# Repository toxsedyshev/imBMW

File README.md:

imBMW · BMW iBus integration SDK and hardware
=========================

[imBMW]: http://imBMW.net "imBMW"
[toxs]: http://toxs.ru "toxs"

[imBMW] is .NET Micro Framework and hardware project. It was started to add custom features to cars with **iBus** interface such as '91-'10 BMWs and some models of Mini, Land Rover, Rover, MG and Rolls Royce. Then **CAN BUS** support was added to integrate with newer F,I,G-series BMWs.

The Original **imBMW V1** device uses **FEZ Mini**, connects with iPod/iPhone via headset cable to be controlled by BMW audio system.

The Next Gen **imBMW V2** device, that uses **STM32F405** based **FEZ Cerb40 II**, is a *duino-compatible iBus-ready board. It could be used with any shield, for example with **imBMW Bluetooth OVC3860** or **Bluetooth Pro Bluegiga WT32 Shields** for wireless stereo audio connection to BMW audio system, handsfree calls and even for forwarding iBus via Bluetooth to smartphones, tablets and PCs - imBMW already has a library for **Universal Windows Platform (UWP)**. There is also **Diagnostic Bus DS2** support using regular OBD II to USB adapter, that allows Engine Control Unit plus additional sensors logging and wireless Bluetooth dashboard. Furthermore, **CAN BUS** support was added for sniffing and integrating with CAN modules of all BMWs since the end 90's till latest BMW models including i-series EVs — for example, CAN BUS integration allowed to [integrate BMW E65 full comfort seats into older BMW E53](https://www.youtube.com/watch?v=P0yJuep_bd4&list=PLDuwqawzvazj9iFQQ9aeggeXeUPphfv94&index=5&pp=gAQBiAQB).

CD-changer emulator and Bordmonitor AUX interface were implemented to connect radio with iPod/iPhone/iPad or with other players, phones and tablets like Windows Phone, Android etc. 
Also imBMW allows communicating with instrument cluster, immobilizer, GM, ZKE, navigation and other modules to receive notifications and control doors, windows, lights, etc.

How to buy imBMW
------------------
**Please note: I used to manufacture and sell imBMW devices but I DON'T sell them anymore.**

You can DIY the project for your personal use as many community members did, some [examples of the device forks are shown here](https://vk.com/album-67915700_260588402).

Social networks
-----------------
* Visit [imBMW YouTube playlist](http://www.youtube.com/playlist?list=PLDuwqawzvazj9iFQQ9aeggeXeUPphfv94) on my channel.
* Official group: [imBMW on vk.com](http://vk.com/imbmw).
* Stay in touch via [imbmw@toxs.ru](mailto:imbmw@toxs.ru), but please remember: I don't sell devices anymore. 
* Photos, videos and creation process of imBMW V1 and V2 devices are located on [e46club.ru forum](http://bmwfanatics.ru/forumvb/viewtopic.php?f=32&t=92399) (for now, only in Russian).

Photos
-

Some screens for example. Playing Bluetooth music, custom bordcomputer, additional features, english and russian UI:  

imBMW compatability
------------------

iBus-compatible cars are listed below:
* BMW 3-series E46, E36*
* BMW 5-series E39, E34*, E60*
* BMW 7-series E38
* BMW 8-series E31*
* BMW X3 E83
* BMW X5 E53
* BMW Z4 E85, E86
* BMW Z8 E52
* MINI Cooper R50, Cooper S R53
* Land Rover Range Rover L30
* Rover 75 R40
* Saab 9-3 2003+

Notes:
* E31 uses different device IDs.
* Last 2 production years of E36 and E34 had iBus-controlled CD43 radio and CD-changers.
* E60 ver. USA had iBus-controlled seat occupation sensor.

imBMW license
------------------

[imBMW] is developed by [toxs] and distributed under Open Source
[CC Attribution Non-Commercial Share Alike License](http://creativecommons.org/licenses/by-nc-sa/3.0/). 
This basically means:
* Licensees may copy, distribute, display and perform the work and make derivative works 
based on it only if they give the author or licensor the credits in the manner specified by these.
* Licensees may copy, distribute, display, and perform the work and make derivative works 
based on it only for noncommercial purposes.
* Licensees may distribute derivative works only under a license identical to the license 
that governs the original work.

© Copyright 2013-2014 [toxs] · All Rights Reserved

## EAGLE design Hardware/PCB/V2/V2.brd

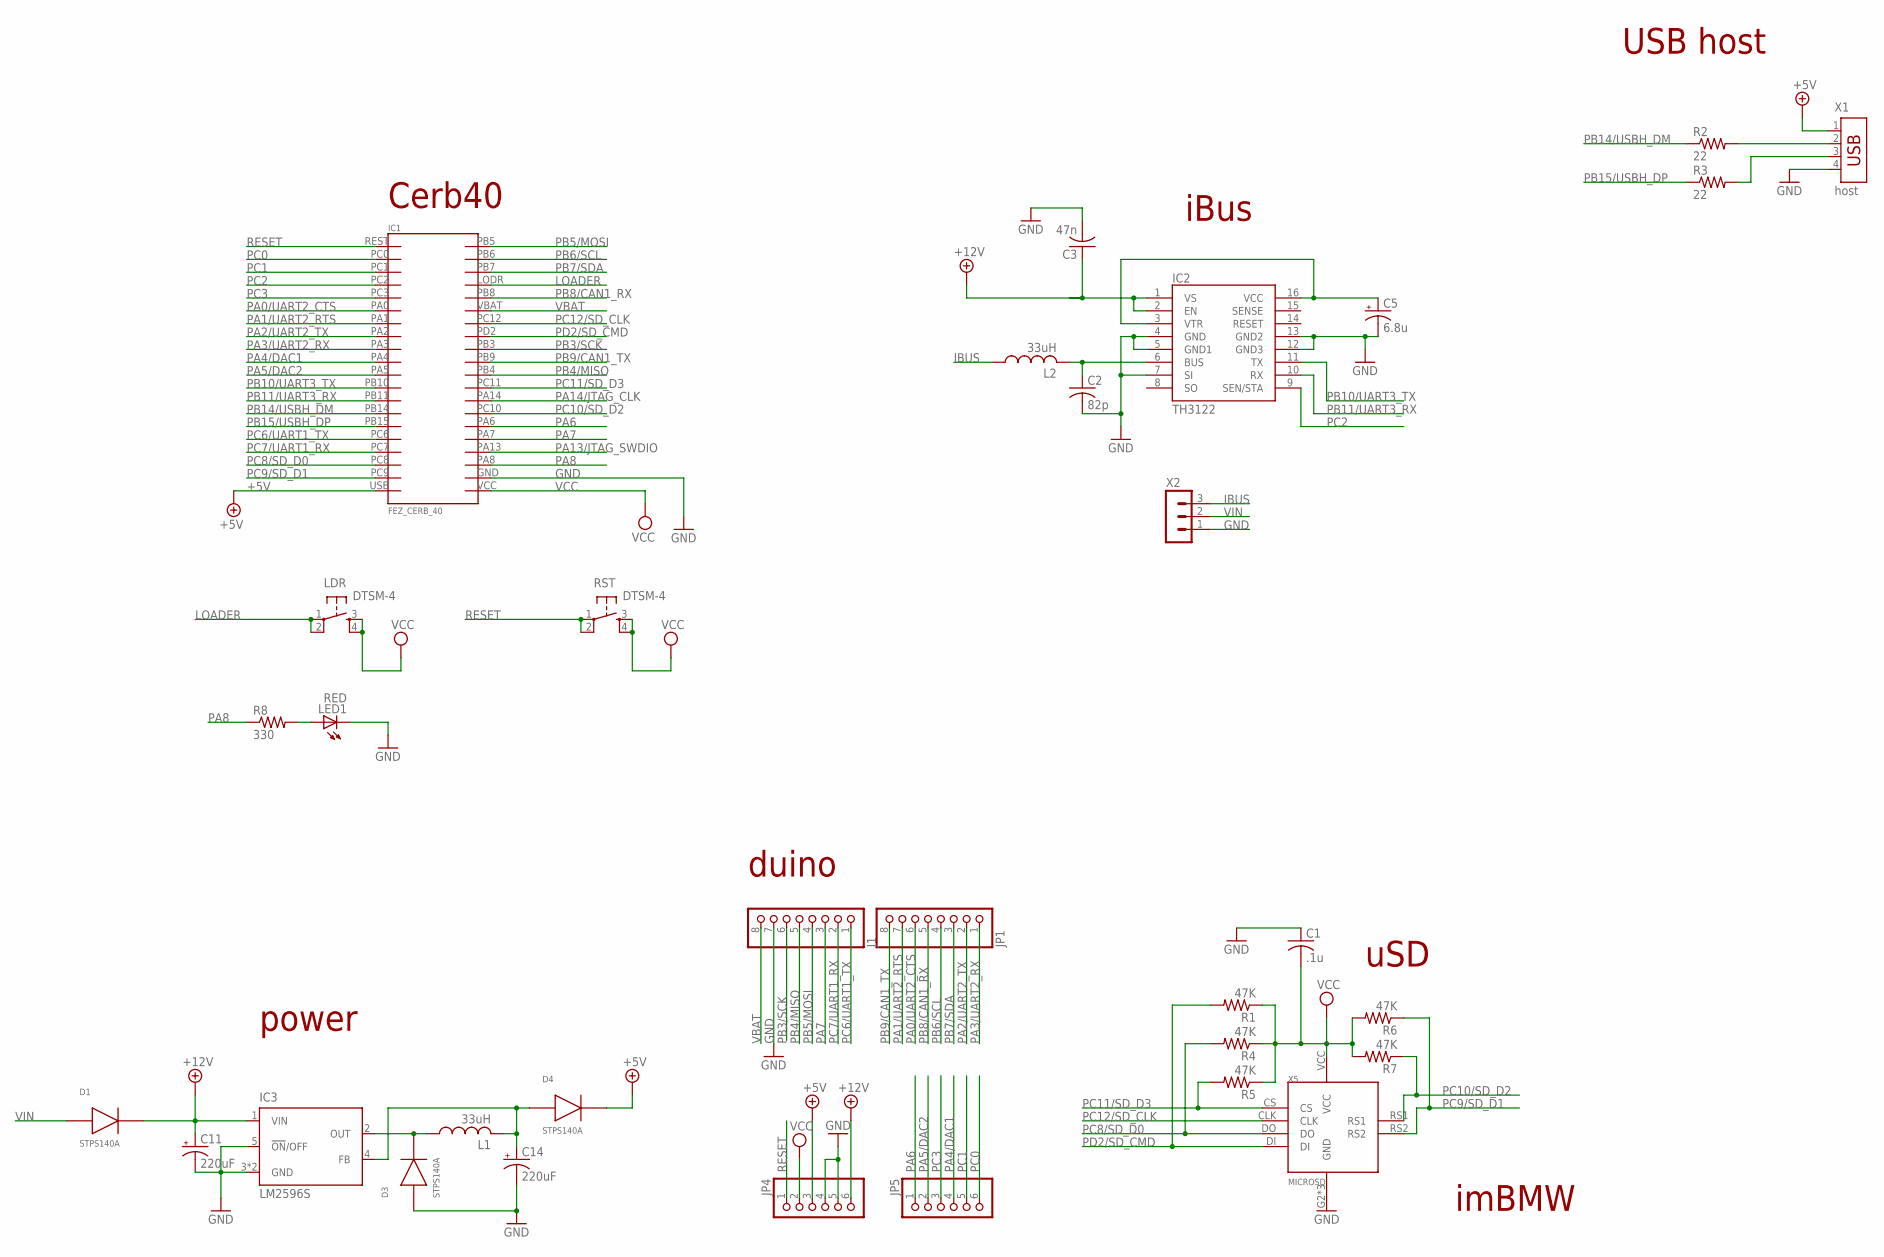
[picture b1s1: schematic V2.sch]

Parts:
C1: .1u; C0805
C2: 82p; C0805
C3: 47n; C0805
C5: 6.8u; SMC_B
C11, C14: 220uF; SMC_D
D1, D3, D4: STPS140A; DIODE_SMA
IC1: FEZ_CERB_40
IC2: TH3122; SO16L
IC3: LM2596S; TO263-5
J1: PINHD-1X8; 1X08
JP1: PINHD-1X8; 1X08
JP4, JP5: PINHD-1X6; 1X06
L1, L2: 33uH; POWER-CHOKE_WE-TPC
LDR: DTSM-4
LED1: RED; SML0603
R1, R4, R5, R6, R7: 47K; R0805
R2, R3: 22; R0805
R8: 330; R0805
RST: DTSM-4
X1: host; USB
X2: MA03-1
X5: MICROSD

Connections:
+5V: D4.K, IC1.USB, JP4.3, X1.1
+12V: C3.1, C11.+, D1.K, IC2.1 (VS), IC2.2 (EN), IC3.1 (VIN), JP4.6
GND: C1.1, C2.2, C3.2, C5.-, C11.-, C14.-, D3.A, IC1.GND, IC2.4 (GND), IC2.5 (GND1), IC2.7 (SI), IC2.12 (GND3), IC2.13 (GND2), IC3.3 (GND), IC3.5 (!ON!/OFF), IC3.6 (GND), J1.7, JP4.4, JP4.5, LED1.C, X1.4, X2.1, X5.G2 (GND), X5.G3 (GND), X5.GND
IBUS: L2.1, X2.3
LOADER: IC1.LODR, LDR.1, LDR.2
unnamed: C14.+, D4.A, IC3.4 (FB), L1.2
unnamed: C2.1, IC2.6 (BUS), L2.2
unnamed: D3.K, IC3.2 (OUT), L1.1
unnamed: C5.+, IC2.3 (VTR), IC2.16 (VCC)
unnamed: LED1.A, R8.2
unnamed: R2.2, X1.2
unnamed: R3.2, X1.3
PA0/UART2_CTS: IC1.PA0, JP1.6
PA1/UART2_RTS: IC1.PA1, JP1.7
PA2/UART2_TX: IC1.PA2, JP1.2
PA3/UART2_RX: IC1.PA3, JP1.1
PA4/DAC1: IC1.PA4, JP5.4
PA5/DAC2: IC1.PA5, JP5.2
PA6: IC1.PA6, JP5.1
PA7: IC1.PA7, J1.3
PA8: IC1.PA8, R8.1
PA13/JTAG_SWDIO: IC1.PA13
PA14/JTAG_CLK: IC1.PA14
PB3/SCK: IC1.PB3, J1.6
PB4/MISO: IC1.PB4, J1.5
PB5/MOSI: IC1.PB5, J1.4
PB6/SCL: IC1.PB6, JP1.4
PB7/SDA: IC1.PB7, JP1.3
PB8/CAN1_RX: IC1.PB8, JP1.5
PB9/CAN1_TX: IC1.PB9, JP1.8
PB10/UART3_TX: IC1.PB10, IC2.11 (TX)
PB11/UART3_RX: IC1.PB11, IC2.10 (RX)
PB14/USBH_DM: IC1.PB14, R2.1
PB15/USBH_DP: IC1.PB15, R3.1
PC0: IC1.PC0, JP5.6
PC1: IC1.PC1, JP5.5
PC2: IC1.PC2, IC2.9 (SEN/STA)
PC3: IC1.PC3, JP5.3
PC6/UART1_TX: IC1.PC6, J1.1
PC7/UART1_RX: IC1.PC7, J1.2
PC8/SD_D0: IC1.PC8, R4.2, X5.DO
PC9/SD_D1: IC1.PC9, R6.1, X5.RS2
PC10/SD_D2: IC1.PC10, R7.1, X5.RS1
PC11/SD_D3: IC1.PC11, R5.2, X5.CS
PC12/SD_CLK: IC1.PC12, X5.CLK
PD2/SD_CMD: IC1.PD2, R1.2, X5.DI
RESET: IC1.REST, JP4.1, RST.1, RST.2
VBAT: IC1.VBAT, J1.8
VCC: C1.2, IC1.VCC, JP4.2, LDR.3, LDR.4, R1.1, R4.1, R5.1, R6.2, R7.2, RST.3, RST.4, X5.VCC
VIN: D1.A, X2.2

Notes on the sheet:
imBMW
uSD
duino
power
USB host
iBus
Cerb40

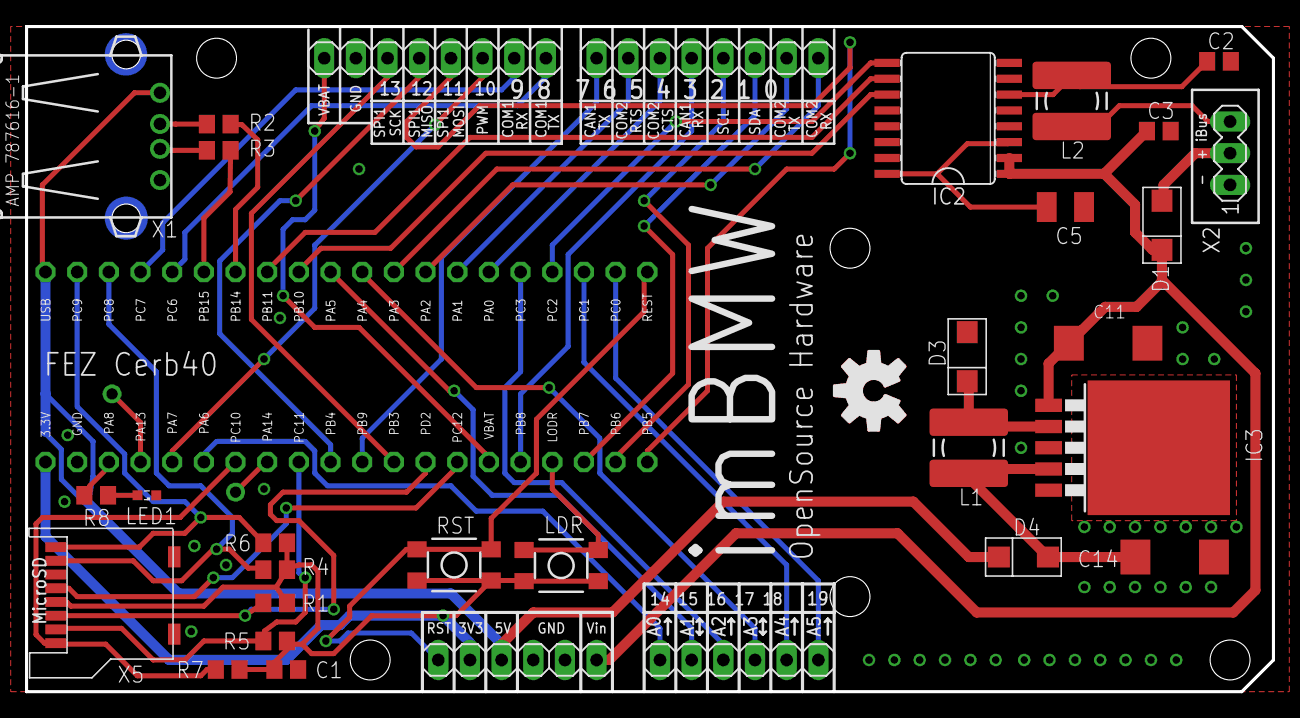
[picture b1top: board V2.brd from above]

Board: 2 copper layers, 100.0 x 53.3 mm, 32 parts (0 on the bottom side), 48 nets.

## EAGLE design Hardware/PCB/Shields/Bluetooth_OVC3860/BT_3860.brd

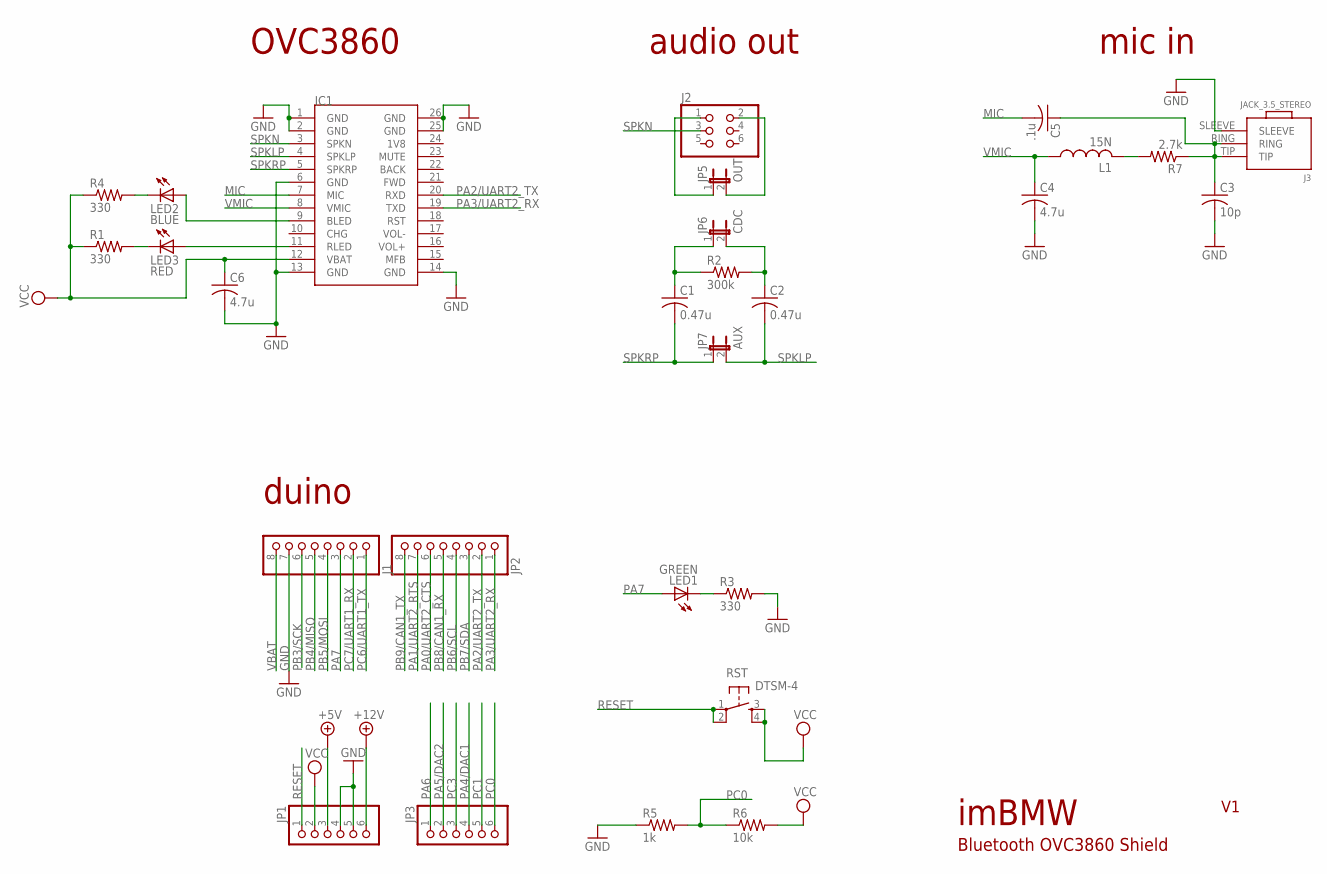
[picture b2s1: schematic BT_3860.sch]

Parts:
C1, C2: 0.47u; C0805
C3: 10p; C0805
C4, C6: 4.7u; C0805
C5: .1u; C0805
IC1: BLK-MD-SPK-B
J1: PINHD-1X8; 1X08
J2: PINHD-2X3; 2X03
J3: JACK_3.5_STEREO
JP1, JP3: PINHD-1X6; 1X06
JP2: PINHD-1X8; 1X08
JP5: OUT; JP1
JP6: CDC; JP1
JP7: AUX; JP1
L1: 15N; L3230M
LED1: GREEN; SML0603
LED2: BLUE; SML0603
LED3: RED; SML0603
R1, R3, R4: 330; R0805
R2: 300k; R0805
R5: 1k; R0805
R6: 10k; R0805
R7: 2.7k; R0805
RST: DTSM-4

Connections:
+5V: JP1.3
+12V: JP1.6
GND: C3.2, C4.2, C6.2, IC1.1 (GND), IC1.2 (GND), IC1.6 (GND), IC1.13 (GND), IC1.14 (GND), IC1.25 (GND), IC1.26 (GND), J1.7, J3.SLEEVE, JP1.4, JP1.5, R3.2, R5.1
MIC: C5.2, IC1.7 (MIC)
unnamed: C2.1, JP6.2, R2.2
unnamed: C1.1, JP6.1, R2.1
unnamed: J2.1, JP5.1
unnamed: J2.2, JP5.2
unnamed: LED1.C, R3.1
unnamed: LED3.C, R1.2
unnamed: IC1.11 (RLED), LED3.A
unnamed: IC1.9 (BLED), LED2.A
unnamed: LED2.C, R4.2
unnamed: C3.1, C5.1, J3.RING, J3.TIP, R7.1
unnamed: L1.2, R7.2
PA0/UART2_CTS: JP2.6
PA1/UART2_RTS: JP2.7
PA2/UART2_TX: IC1.20 (RXD), JP2.2
PA3/UART2_RX: IC1.19 (TXD), JP2.1
PA4/DAC1: JP3.4
PA5/DAC2: JP3.2
PA6: JP3.1
PA7: J1.3, LED1.A
PB3/SCK: J1.6
PB4/MISO: J1.5
PB5/MOSI: J1.4
PB6/SCL: JP2.4
PB7/SDA: JP2.3
PB8/CAN1_RX: JP2.5
PB9/CAN1_TX: JP2.8
PC0: JP3.6, R5.2, R6.1
PC1: JP3.5
PC3: JP3.3
PC6/UART1_TX: J1.1
PC7/UART1_RX: J1.2
RESET: JP1.1, RST.1, RST.2
SPKLP: C2.2, IC1.4 (SPKLP), JP7.2
SPKN: IC1.3 (SPKN), J2.3
SPKRP: C1.2, IC1.5 (SPKRP), JP7.1
VBAT: J1.8
VCC: C6.1, IC1.12 (VBAT), JP1.2, R1.1, R4.1, R6.2, RST.3, RST.4
VMIC: C4.1, IC1.8 (VMIC), L1.1

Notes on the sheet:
imBMW
duino
Bluetooth OVC3860 Shield
OVC3860
audio out
mic in

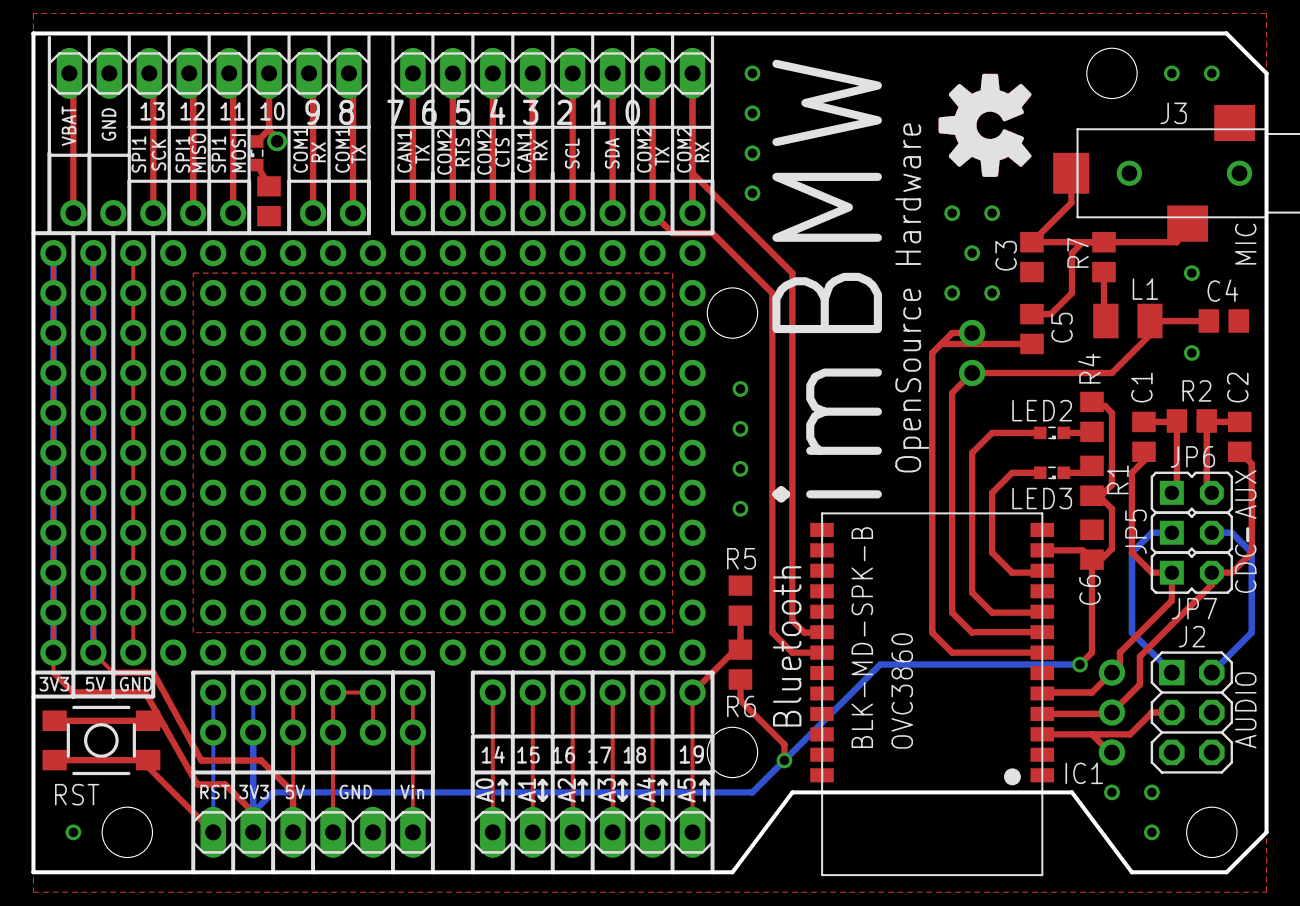
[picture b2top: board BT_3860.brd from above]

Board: 2 copper layers, 78.4 x 53.3 mm, 28 parts (0 on the bottom side), 23 nets.

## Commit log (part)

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2013-01-05 Readme added
2013-01-07 Added iPod control
2013-01-10 Connected MFL to iPod, added iBus messages descriptions
2013-01-11 Fixed RT press, cleaned up Program.cs
2013-01-11 Fixed Dial long press
2013-01-11 Removed unnecessary sleep
2013-01-12 Added CDC play/pause, fixed Dial long press, added status displaying
2013-01-15 IKE logic moved to its own class
2013-01-16 MFL logic moved to its own class
2013-01-18 Schematics and PCB design added
2013-01-24 ManualResetEvent added to QueueThreadWorker
2013-01-26 PCB updated
2013-01-28 Added display text for playing state fix by RND button
2013-01-29 QueueWorkerThread priority fix
    Trying to fix *ResetEvent slowness
2013-01-29 ClassDiagram added and PCB updated
2013-02-03 Cleaned up the code
2013-02-04 Logger added
2013-02-05 License changed
2013-02-05 GC logs turned off
2013-02-17 Clear radio display on turning off
2013-02-17 iPod logic moved to its own class
2013-02-25 Trunk opening added.
2013-02-28 Readme changed
2013-03-01 imBMW library and imBMW V1 device separated to different projects
2013-03-01 IKE: Speed&RPM. Doors: lock/unlock.
2013-03-01 Feature: Close doors on 5km/h, open on ignition off
2013-03-01 Feature: close windows and sunroof when car is locked from remote.
2013-03-04 Fixed ignition, created Comfort Features class
    ...for auto open/close doors, windows, sunroof, mirrors
2013-03-07 Added message received/sent events, description
2013-03-09 iBus manager fixes
    Write enqueue recursion, read queue, anti-flood 20ms
2013-03-10 Readme fix
2013-03-15 Write anti-flood changed to 5ms, read processing moved to the main thread
2013-03-19 SerialPorts fixes
2013-03-22 Batch iBus sending, PerformanceInfo, SampleFeatures
2013-03-22 SerialInterruptPort glitch fix, QueueThreadWorker normal priority
2013-03-28 SerialPorts fixes and optimization. Some cleanup
2013-03-30 iBus batch read, SerialPorts fixes, SerialPortHub works
2013-03-30 SerialPortHub fix
2013-03-31 Logs deleted
2013-03-31 Comfort features commands queue. Blink LED on I/O.
2013-04-03 SerialPortBase.WriteTimeout renamed to AfterWriteDelay
2013-04-12 ReadMe updated
2013-04-26 iBus optopair adapter pcb added
2013-04-29 iBus optopair adapter pcb updated
2013-05-07 XPS for toner transfer method of V1 PCB added
2013-05-12 Added LightControlModule and some fixes
2013-07-21 iBus AfterWriteDelay fix, CDC play/pause fix, comfort close fix
2013-11-29 Initial commit of V2
2013-11-29 SerialPorts (OptoPair). Some other fixes.
    SerialInterruptPortBase, SerialPortOptoPair, SerialTimerInterruptPort
2013-12-27 Added support of BT OVC3860
    Bluetooth module Bolutek BLK-MD-SPK-B based on OmniVision OVC3860
2014-01-07 Bluetooth fixes
2014-02-01 Added Bordmonitor support (partial), Russian text
    and other fixes
2014-02-20 Little fix: namespace changed
2014-02-22 Extending platform
    Added SeatMemory, Navigation IBus device message parsing.
2014-02-22 AUX detection, players' events displaying
2014-03-18 Find device on iBus, Bluetooth fixes, Contacts parsing, Temperature, Voltage
    Unstable
2014-03-20 Custom BC fixes
2014-03-21 Readme fixed
2014-03-21 Readme changed. Again
2014-04-03 Added screenshot to readme.
2014-04-21 Bordmonitor menu. MID screen. Sheilds (draft).
2014-04-27 BM menu fixes.
2014-05-04 Rad menu flickering fix. Bordcomputer and settings screens. BT connect fix and contacts screen. Localization. CDC fix. Door and key commands. Temp fix.
2014-05-05 Remote key buttons fix
2014-05-05 CDC+AUX=MediaEmulator.
    Not tested!
2014-05-06 MB menu flickering fixes. CDC emulation fixes. Init fixed.
    + Driver door lock. Gong messages. Menu checkbox fixes.
    Not tested!
2014-05-06 CDC emulation fixes. BT connect&play fix.
2014-05-06 Added version info.
2014-05-06 [SW V1.0] Added hex binaries
2014-05-06 Some strings
2014-05-19 Code cleanup, added additional modules
2014-05-19 Revert back changes to original distribution
2014-05-22 MenuScreenUpdateReason, Settings, etc..
    ..lock/unlock doors fixes, contacts reading refactored, FileLogger
    (unstable)
2014-05-23 RadioMenu added, Contacts fixed, MK2 fixed, V1 device updated
2014-05-23 RadioMenu BC fix
2014-05-27 RadioMenu fixes, .NET MF 4.1 fixes
2014-05-28 BC voltage auto update
2014-05-28 Added HW2 FW1.0.3 build
2014-06-05 Radio menu: track change fixed, BC screen fixed.
2014-06-08 Radio menu track change fixed
2014-06-08 Added HW2 FW1.0.5 build
2014-06-15 Readme images changed
2014-06-30 BordmonitorMenu and RadioMenu fixed
2014-07-16 Added HW2 FW1.0.7 build
2014-07-19 Radio MFL navigation fixed. Device V2 pins added. Tests added.
2014-07-19 Bordmonitor batch writing.
2014-07-19 BC voltage fix.
2014-07-19 GM5 unlock fix
2014-07-19 Added HW2 FW1.0.8 build
2014-09-03 Bordmonitor batch screen update in single message
2014-09-03 Added HW2 FW1.0.9 build
2014-10-19 Project structure changed
2014-10-19 Added V2 and Bluetooth OVC3860 Eagle projects. Added case projects. Builds moved.
2014-10-31 Bluetooth WT32 initial work.
2014-11-04 WT32 implemented as AudioPlayer.
2014-11-06 NowPlaying WT32 parsing.
2014-11-06 Translit and Yo ASCII support added for Russian. NowPlaying on Bordmonitor fixed.
2014-11-07 WT32 fixes. Menu fixes.
2014-11-09 Fixed iBus message max length.
2014-11-09 WT32 MUX mode.
2014-11-11 UTF8 to ASCII optimized.
2014-11-11 Added support for player settings status event.
2014-11-12 SerialInterruptPort fixed.
2014-11-12 iBus.Manager can send raw messages.
2014-11-12 WT32 SPPLink added.
2014-11-14 .NET MF library preparations for Portable .NET library. InternalMessage.
2014-11-14 .NET Portable library initial commit.
2014-11-14 WindowsPhone/Windows Universal App initial commit.
2014-11-14 iBus.Manager static constructor fixes.
2014-11-14 SPPLink fix.
2014-11-14 BluetoothClient added to imBMW.Portable.
2014-11-21 Bordmonitor show text events.
2014-11-21 PCL BT Client fixes.
2014-11-21 WindowsApp BT connection. Bordmonitor and Test pages.
2014-11-23 Comfort windows fixed to prevent ignoring by ZKE.
2014-11-23 BM<>Radio buttons and events.
2014-11-23 SharedApp Bordmonitor and Test Pages fixed.
2014-11-24 SharedApp logger fixed.
2014-11-24 BM&Radio commands fixed.
2014-11-24 WT32 pin change support.
2014-11-24 SocketClient fixed.
2014-11-24 SharedApp: assets updated.
2014-11-24 BluetoothPin added to settings.
2014-11-24 MediaShield setting added.
2014-11-24 InternalCommunications.
2014-11-24 MessageParser used in SocketClient.
2014-11-26 Readme changed.
2015-01-22 Build 1.0 files renamed
2015-01-22 Full windows open command fixed
2015-01-22 PCL logger implemented
2015-01-22 Added Init() for static iBus device classes
2015-01-22 Bordmonitor fixed item indexes and parsing
2015-01-22 SharedApp: LoggerPage added
2015-02-01 V2 device pins refactored.
2015-02-01 Manager.FindDevice refactored with ManualResetEvent
2015-04-03 Unlock doors after driver door opened reverted.
2015-04-10 Device.V1 .NET MF 4.1 memory limit fixes
2015-06-11 OVC3860 autoplay fixed.
2015-06-11 WT32 HFP enabled.
2015-06-11 Some non-functional fixes.
2015-06-11 Version string fixed.
2015-06-11 Added HW2 FW1.0.10 build
2015-07-09 MK2 and MK3 menu drawing fixed.
2015-07-10 Added HW2 FW1.0.11 build
2015-09-17 Updated to GHI SDK 2015 R1 (4.3.7.10)
2015-10-12 DBus DS2 initial commit
2015-10-13 NETMF 4.1 fixed V1.Program and StringHelpers
2015-10-14 DBus moved to separate project. MS43 analog values parsing started.
2015-10-14 MS43 analog values parsed
2015-10-19 MS43 logger strings and fixes
2015-10-23 Added JMGarage patched DME diag parser
2015-11-24 Fixed iBus.Message checksum
2015-11-24 Date&Time and BC parsing
    Partly merged huge pull request by @arctus
2016-04-05 DateTime parsing fixed for US locale.
2016-04-05 MID menu buttons added.
2016-04-05 QueueThreadWorker made public.
2016-04-10 DateTime parse 12PM fixed.
2016-04-14 Added mask to MID menu last buttons.
2016-04-14 Fixed battery voltage on BC.
2016-04-14 BC: unset values fixed and unchanged events not fired.
2016-04-15 BC: added original BC values to BC screen.
2016-04-20 Main imBMW project splitted to multiple projects.
    To reduce dlls size - .NET MF limit.
2016-04-21 Bordmonitor translit fix.
2016-04-21 BC limit fix.
2016-04-21 Readme changed with new BC screens.
2016-04-21 BC: unset values fixed.
2016-04-21 Added HW2 FW1.0.12 build
2016-06-12 Diagnostic fixes and cleanup.
2016-06-12 Some cleanup.
2016-06-12 Starting to port PCL to UWP.
2016-07-27 Starting the Dashboard.
2016-08-04 Gauges updated.
2016-08-05 Gauge updated.
2016-08-05 PieSlice double gauge support.
2016-08-08 DoubleGauge implemented.
2016-08-10 Default settings for gauges.
2016-08-10 Dashboard fixes.
2016-08-12 TestGauges fixed.
2016-08-14 Dashboard link from Home.
2016-08-14 DBus message fixes.
2016-08-14 Messages fixed.
2016-08-14 GaugeWatcher fixed.
2016-08-15 Dashboard fixed.
2016-08-15 DBusMessageParser fixed.
2016-08-15 UWP Hashtable fix.
2016-08-15 Mobile Dashboard added.
2016-08-15 Some fixes for UWP App.
2016-08-16 SecondaryGauge update by GaugeField fix.
2016-11-29 RadioMenu RT mode fix.
2016-11-29 UWP app updated.
2017-03-30 MFL player control fixed with CDC and Bordmonitor.
2017-03-30 Cerberus parity bug fixed in the firmware. Finally.
2018-01-22 BC fix for non-E46 IKEs
    By @windel12
2018-03-07 Gauges refactored (partly)
2018-03-07 Partial revert of a21c8ff commit
2018-04-16 References updated.
2018-08-22 CAN BUS adapters implementation.
    Native GHI NETMF and MCP2515 CAN BUS adapters added.
2018-08-28 CAN adapters refactored. Custom timings.
2018-09-24 CAN BUS fixes.
2018-09-24 E65 seats CAN BUS emulation.
    Emulation of CAN BUS "wakeup" messages to make E65 "comfort" seats work.
    Partly implemented.
2018-09-26 E65 seats full emulation.
2018-10-18 E65 seats emulation fixed and menu added. Light dimmer.
2019-01-10 Don't scroll screen to top on wake up.
2019-01-10 BordmonitorAUX refactoring.
2019-01-10 Added some E65 seats movement control commands.
2019-01-10 MID AUX initial commit.
2019-01-11 Seats emulator fix.
2019-01-11 MID AUX partially finished.
2019-01-12 Show menu on IKE (preparations).
2019-01-15 Shorten incoming call number.
2019-01-15 Menu fix for CDC emu.
2019-01-16 BC fixes for non-e46.
2019-01-16 Request DateTime And Set Local.
2019-01-16 IKE.EngineStarted event.
2019-01-16 E65 seats auto heater activation.
2019-02-01 Radio<>CDC testing.
2019-02-01 Radio<>CDC fixes.
2019-02-05 GetDateTIme fix.
2019-02-05 CDC emulator BM54 fix.
2019-02-05 Device launcher.
2019-02-05 Can Bus MCP2515 adapter deprecated.
2019-02-05 Show screen on multiple menus.
2019-02-06 Launcher fixes.
2019-02-06 Launcher wording fixes.
2019-02-08 Device projects directories renamed.
2019-02-08 Wording fix.
2019-02-19 CDC announce removed.
2019-02-21 Media shield init logging.
2019-04-01 MCP2515 CAN tranceiver is deprecated.
2019-04-01 Math class renamed.
2019-04-01 imBMW BlackBox DME analog values.
2019-04-02 UWP fixes.
2019-04-02 Message parser fixes.
2019-04-03 NETMF<>UWP fix.
2019-04-03 UWP: Finally fixed gauges.
    At least one works, again :)
2019-04-03 Added all MS43 + BlackBox sensors gauges.
2019-04-05 Huge messaging refactoring.
2019-04-05 UWP: Gauges appearance fixed.
2019-04-05 UWP: Little meth gauge fix.
2019-04-07 Navigation data.
    Partially merged PR #3 by @arctus.
2019-04-07 Logger parameters added.
2019-04-22 UWP: Prevent sleep mode when connected.
2019-05-08 Menu improvements and fixes.
2019-05-08 E65 seats more features.
    Ventilation, massage, move&tilt.
2019-05-14 E65 seats status.
2019-05-24 E65 seats ventilation auto activation.
2019-07-15 Added CSU iBus device.
2019-08-31 UWP app gauges changed.
2019-08-31 FW version changed.
2019-08-31 Added build HW2 FW1.1.13.
2021-03-15 NETMF SDK added.
2021-05-24 CanBus refactoring and optimizations.
    CanBus read queue is NOT optimized yet for high load.
2021-05-24 Junk data removed from canbus packet.
